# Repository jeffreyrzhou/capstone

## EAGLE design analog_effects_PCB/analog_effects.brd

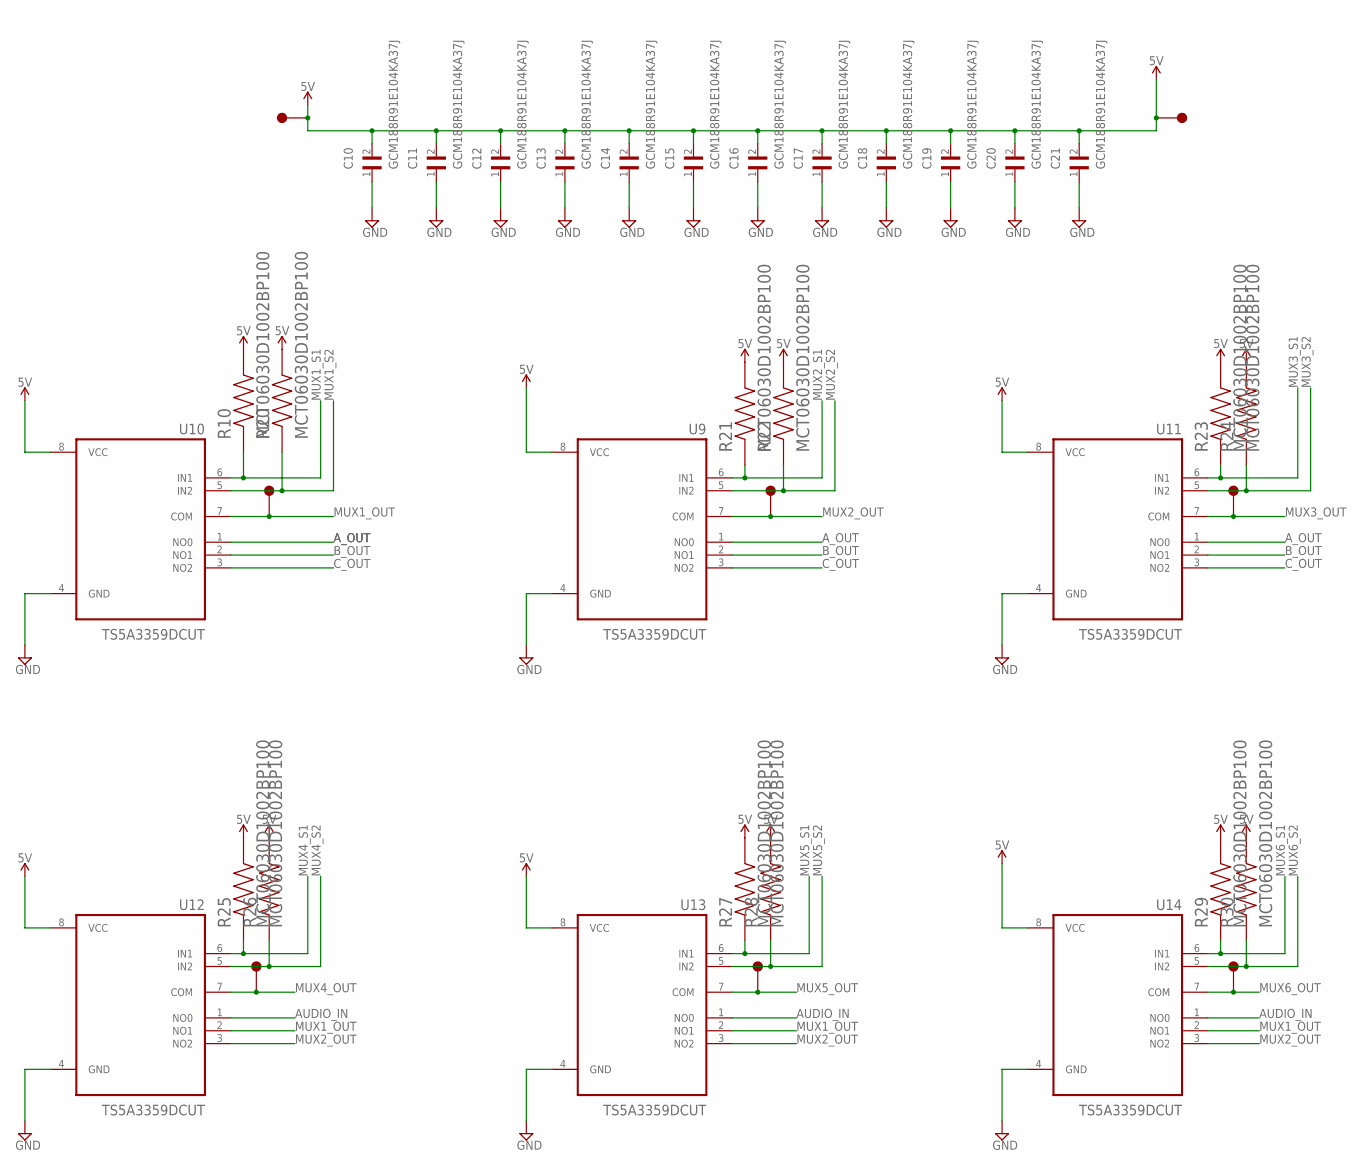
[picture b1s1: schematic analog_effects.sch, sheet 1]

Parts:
C10, C11, C12, C13, C14, C15, C16, C17, C18, C19, C20, C21: GCM188R91E104KA37J; CAPC1608X90N
R10, R20, R21, R22, R23, R24, R25, R26, R27, R28, R29, R30: MCT06030D1002BP100; RESC1508X55N
TP13, TP14, TP15, TP16, TP17, TP18, TP19, TP20: 5015; KEYSTONE_5015
U9, U10, U11, U12, U13, U14: TS5A3359DCUT; SOP50P310X90-8N

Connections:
5V: C10.2, C11.2, C12.2, C13.2, C14.2, C15.2, C16.2, C17.2, C18.2, C19.2, C20.2, C21.2, R10.2, R20.2, R21.2, R22.2, R23.2, R24.2, R25.2, R26.2, R27.2, R28.2, R29.2, R30.2, TP19.1, TP20.1, U9.8 (VCC), U10.8 (VCC), U11.8 (VCC), U12.8 (VCC), U13.8 (VCC), U14.8 (VCC); also elsewhere on the board
AUDIO_IN: U12.1 (NO0), U13.1 (NO0), U14.1 (NO0); also elsewhere on the board
A_OUT: U9.1 (NO0), U10.1 (NO0), U11.1 (NO0); also elsewhere on the board
B_OUT: U9.2 (NO1), U10.2 (NO1), U11.2 (NO1); also elsewhere on the board
C_OUT: U9.3 (NO2), U10.3 (NO2), U11.3 (NO2)
GND: C10.1, C11.1, C12.1, C13.1, C14.1, C15.1, C16.1, C17.1, C18.1, C19.1, C20.1, C21.1, U9.4 (GND), U10.4 (GND), U11.4 (GND), U12.4 (GND), U13.4 (GND), U14.4 (GND); also elsewhere on the board
MUX1_OUT: TP16.1, U10.7 (COM), U12.2 (NO1), U13.2 (NO1), U14.2 (NO1)
MUX1_S1: R10.1, U10.6 (IN1); also elsewhere on the board
MUX1_S2: R20.1, U10.5 (IN2); also elsewhere on the board
MUX2_OUT: TP17.1, U9.7 (COM), U12.3 (NO2), U13.3 (NO2), U14.3 (NO2)
MUX2_S1: R21.1, U9.6 (IN1); also elsewhere on the board
MUX2_S2: R22.1, U9.5 (IN2); also elsewhere on the board
MUX3_OUT: TP18.1, U11.7 (COM)
MUX3_S1: R23.1, U11.6 (IN1); also elsewhere on the board
MUX3_S2: R24.1, U11.5 (IN2); also elsewhere on the board
MUX4_OUT: TP13.1, U12.7 (COM); also elsewhere on the board
MUX4_S1: R25.1, U12.6 (IN1); also elsewhere on the board
MUX4_S2: R26.1, U12.5 (IN2); also elsewhere on the board
MUX5_OUT: TP14.1, U13.7 (COM); also elsewhere on the board
MUX5_S1: R27.1, U13.6 (IN1); also elsewhere on the board
MUX5_S2: R28.1, U13.5 (IN2); also elsewhere on the board
MUX6_OUT: TP15.1, U14.7 (COM); also elsewhere on the board
MUX6_S1: R29.1, U14.6 (IN1); also elsewhere on the board
MUX6_S2: R30.1, U14.5 (IN2); also elsewhere on the board

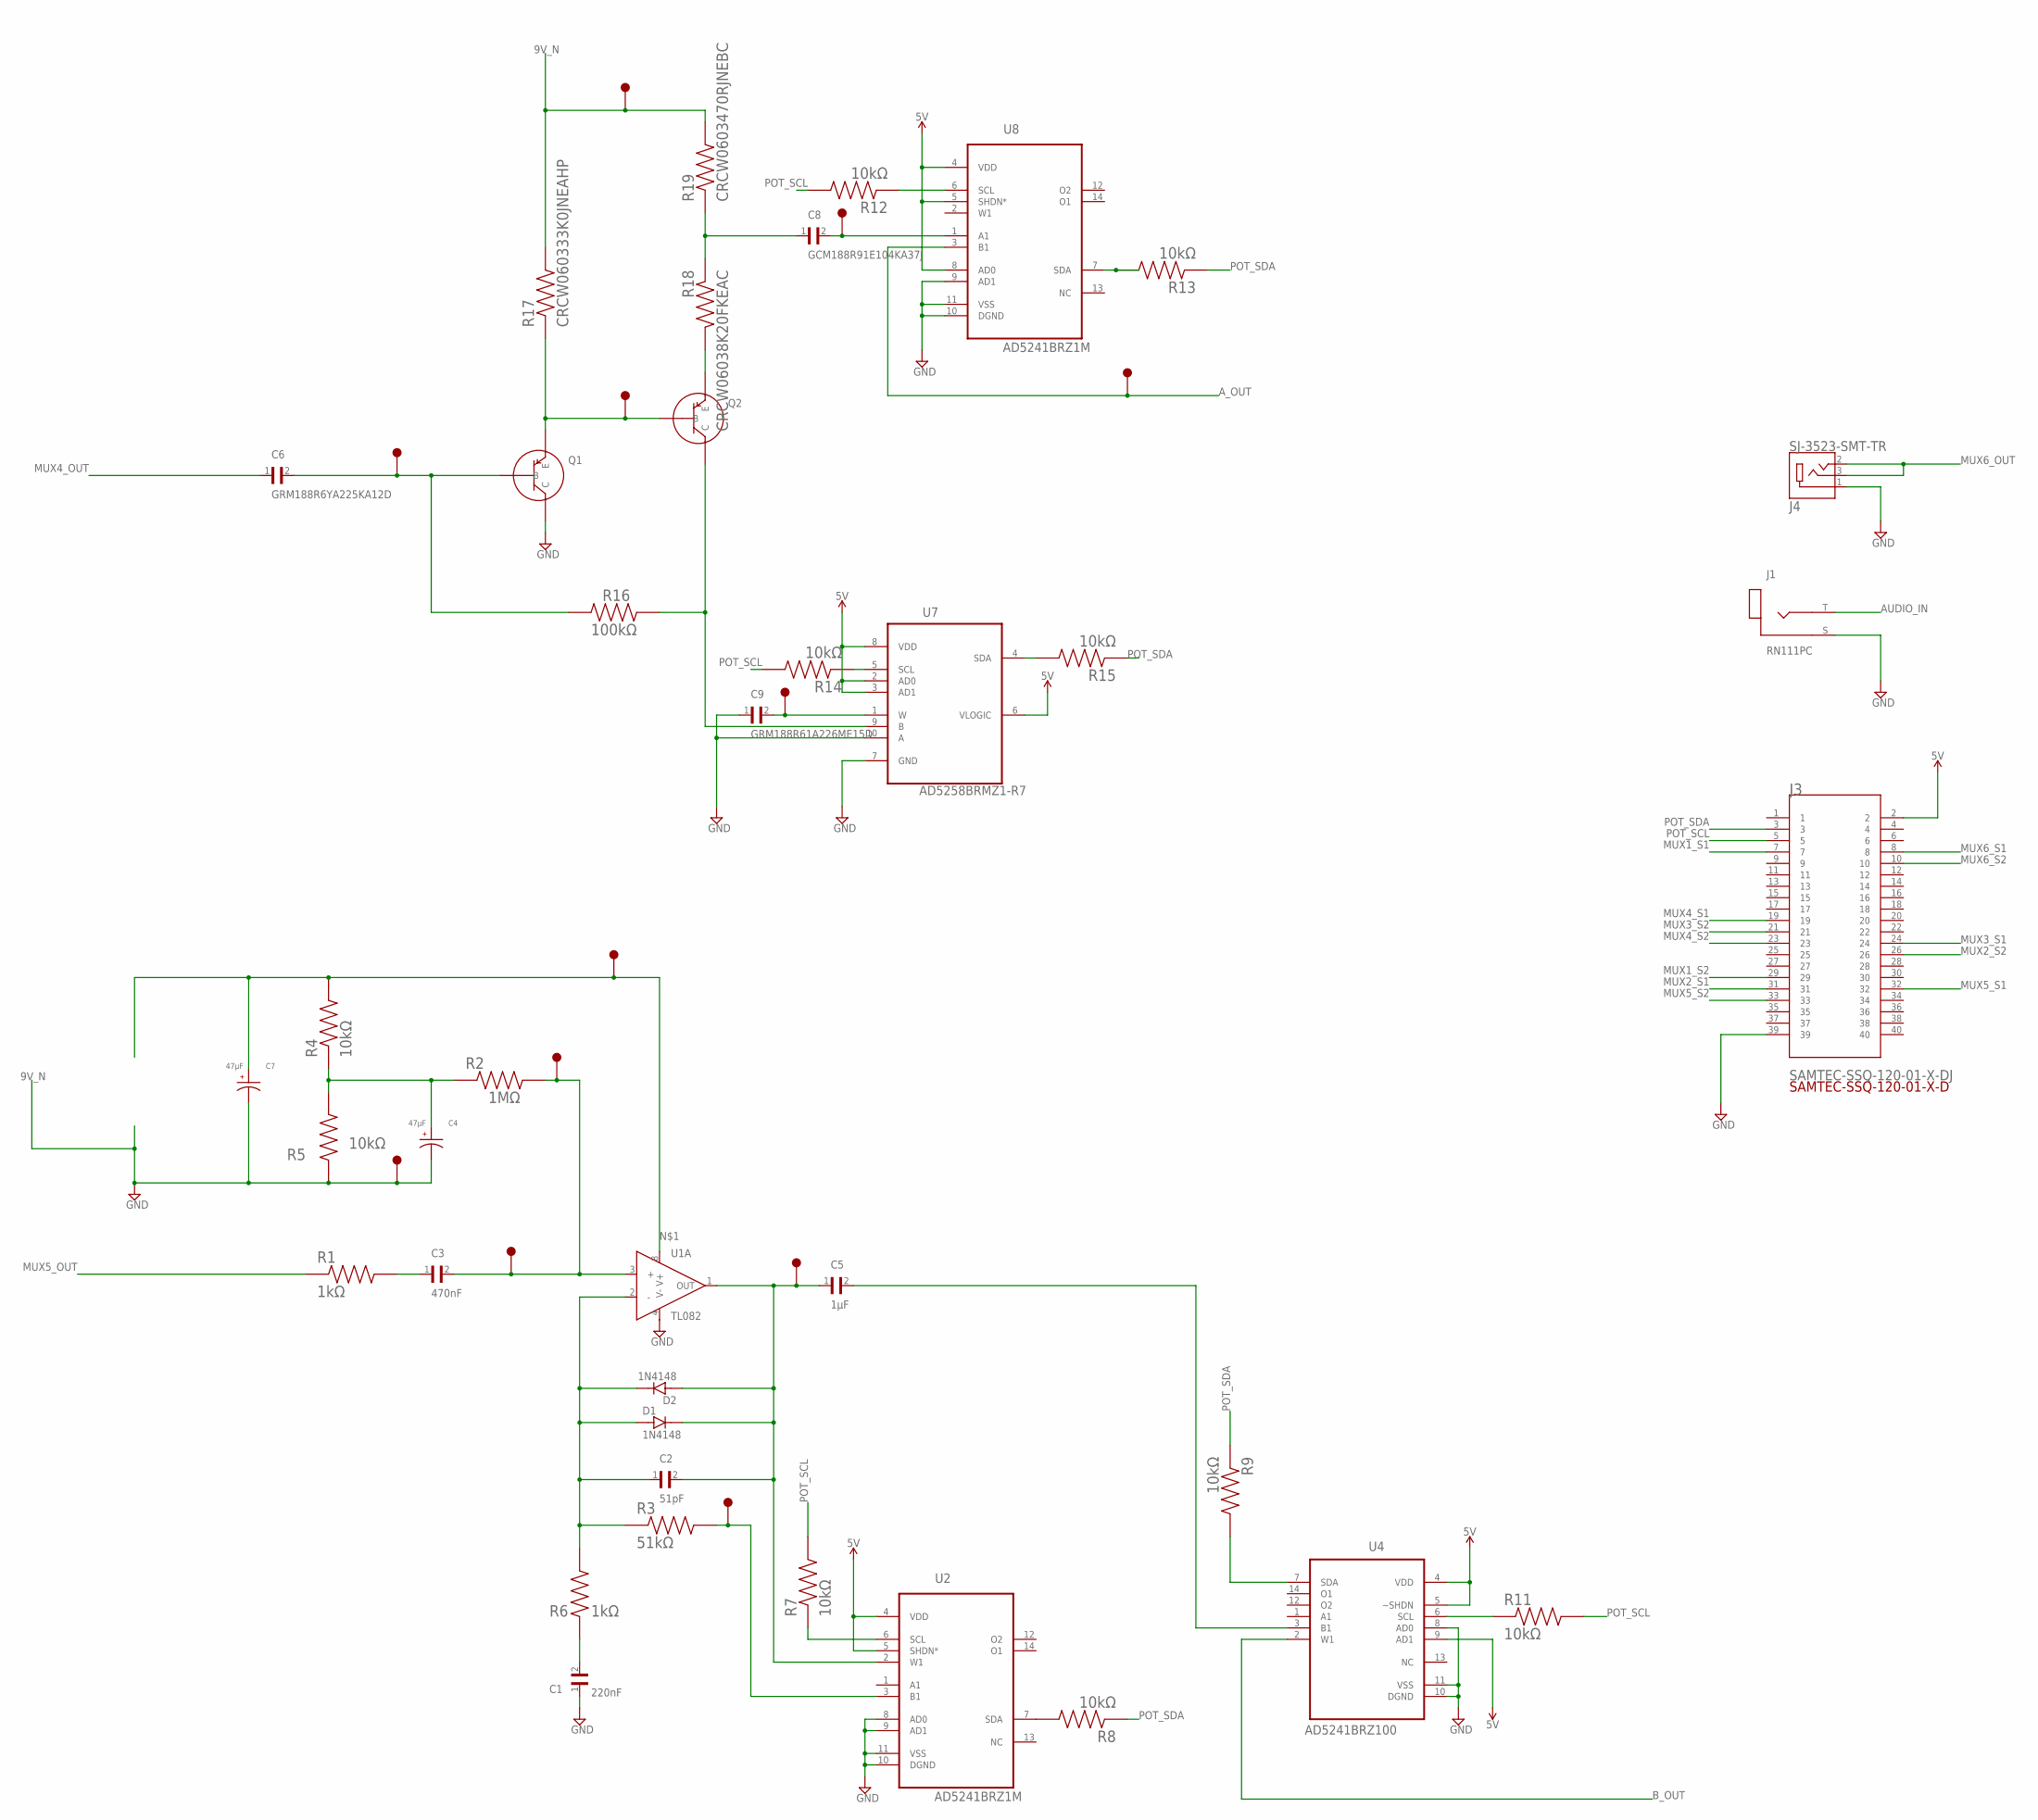
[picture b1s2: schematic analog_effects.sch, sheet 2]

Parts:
C1: 220nF; CAPC3325X94N
C2: 51pF; CAPC1608X87N
C3: 470nF; CAPC1608X95N
C4, C7: 47μF; CAPAE660X800N
C5: 1μF; CAPC1608X90N
C6: GRM188R6YA225KA12D; CAPC1608X90N
C8: GCM188R91E104KA37J; CAPC1608X90N
C9: GRM188R61A226ME15D; CAPC1608X100N
D1, D2: 1N4148; DIOAD829W49L456D191
J1: RN111PC; SWITCHCRAFT_RN111PC
J3: SAMTEC-SSQ-120-01-X-DJ; SAMTEC-SSQ-120-01-X-D
J4: SJ-3523-SMT-TR; CUI_SJ-3523-SMT-TR
R1, R6: 1kΩ; RESC1508X55N
R2: 1MΩ; RESC1608X55N
R3: 51kΩ; RESC1608X55N
R4, R5, R7, R8, R9, R11, R12, R13, R14, R15: 10kΩ; RESC1508X55N
R16: 100kΩ; RESC1508X50N
R17: CRCW060333K0JNEAHP; RESC1608X55N
R18: CRCW06038K20FKEAC; RESC1608X55N
R19: CRCW0603470RJNEBC; RESC1608X55N
TP1, TP2, TP3, TP4, TP5, TP6, TP7, TP8, TP9, TP10, TP11, TP12: 5015; KEYSTONE_5015
U1: TL082; SOIC127P600X175-8N
U2, U8: AD5241BRZ1M; SOIC127P600X175-14N
U4: AD5241BRZ100; SOIC127P600X175-14N
U7: AD5258BRMZ1-R7; SOP50P490X110-10N

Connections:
5V: J3.2, U2.4 (VDD), U2.5 (SHDN*), U4.4 (VDD), U4.5 (~SHDN), U4.9 (AD1), U7.2 (AD0), U7.3 (AD1), U7.6 (VLOGIC), U7.8 (VDD), U8.4 (VDD), U8.5 (SHDN*), U8.8 (AD0); also elsewhere on the board
9V_N: C4.2, C7.2, R5.1, R17.2, R19.2, TP2.1, TP9.1
AUDIO_IN: J1.T; also elsewhere on the board
A_OUT: TP12.1, U8.3 (B1); also elsewhere on the board
B_OUT: U4.2 (W1); also elsewhere on the board
GND: C1.1, C9.1, J1.S, J3.39, J4.1, U1.4 (V-), U2.8 (AD0), U2.9 (AD1), U2.10 (DGND), U2.11 (VSS), U4.8 (AD0), U4.10 (DGND), U4.11 (VSS), U7.7 (GND), U7.10 (A), U8.9 (AD1), U8.10 (DGND), U8.11 (VSS); also elsewhere on the board
MUX1_S1: J3.7; also elsewhere on the board
MUX1_S2: J3.29; also elsewhere on the board
MUX2_S1: J3.31; also elsewhere on the board
MUX2_S2: J3.26; also elsewhere on the board
MUX3_S1: J3.24; also elsewhere on the board
MUX3_S2: J3.21; also elsewhere on the board
MUX4_OUT: C6.1; also elsewhere on the board
MUX4_S1: J3.19; also elsewhere on the board
MUX4_S2: J3.23; also elsewhere on the board
MUX5_OUT: R1.1; also elsewhere on the board
MUX5_S1: J3.32; also elsewhere on the board
MUX5_S2: J3.33; also elsewhere on the board
MUX6_OUT: J4.2, J4.3; also elsewhere on the board
MUX6_S1: J3.8; also elsewhere on the board
MUX6_S2: J3.10; also elsewhere on the board
unnamed: C7.1, R4.2, TP5.1, U1.8 (V+)
unnamed: C4.1, R2.1, R4.1, R5.2
unnamed: C2.1, D1.A, D2.C, R3.1, R6.2, U1.2 (-)
unnamed: C3.1, R1.2
unnamed: C2.2, C5.1, D1.C, D2.A, TP1.1, U1.1 (OUT), U2.2 (W1)
unnamed: C3.2, R2.2, TP3.1, TP4.1, U1.3 (+)
unnamed: C1.2, R6.1
unnamed: C6.2, R16.1, TP7.1
unnamed: R17.1, TP8.1
unnamed: R8.2, U2.7 (SDA)
unnamed: R3.2, TP6.1, U2.3 (B1)
unnamed: R12.1, U8.6 (SCL)
unnamed: R9.2, U4.7 (SDA)
unnamed: R7.1, U2.6 (SCL)
unnamed: C8.1, R18.1, R19.1
unnamed: R13.2, U8.7 (SDA)
unnamed: R14.1, U7.5 (SCL)
unnamed: R11.1, U4.6 (SCL)
unnamed: C5.2, U4.3 (B1)
unnamed: R15.2, U7.4 (SDA)
unnamed: R16.2, U7.9 (B)
unnamed: C9.2, TP11.1, U7.1 (W)
unnamed: C8.2, TP10.1, U8.1 (A1)
POT_SCL: J3.5, R7.2, R11.2, R12.2, R14.2
POT_SDA: J3.3, R8.1, R9.1, R13.1, R15.1

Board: 4 copper layers, 87 parts (0 on the bottom side), 50 nets, no tracks yet.

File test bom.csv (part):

"Part";"Value";"Device";"Package";"Description";"AVAILABILITY";"COMMENT";"CUI_PURCHASE_URL";"DESCRIPTION";"DIGI-KEY_PART_NUMBER";"EU_ROHS_COMPLIANCE";"MF";"MP";"PACKAGE";"POWER_RATING";"PRICE";"PURCHASE-URL";"RESISTANCE";"SPICEPREFIX";"TOLERANCE";"VOLTAGE_RATING";
"C1";"220nF";"12105C224MAT2A";"CAPC3325X94N";"Cap Ceramic 0.22uF 50V X7R 20% SMD 1210 125°C Paper T/R Check prices";"Good";"";"";" 1210 220 nF 50 V ±20 % Tolerance X7R SMT Multilayer Ceramic Capacitor ";"";"";"AVX";"12105C224MAT2A";"3325 AVX";"";"None";"https://pricing.snapeda.com/search/part/12105C224MAT2A/?ref=eda";"";"";"";"";
"C2";"51pF";"C0603C510F1GACTU";"CAPC1608X87N";"Cap Ceramic 51pF 100V C0G 1% SMD 0603 125°C Paper T/R Check prices";"Bad";"";"";" Cap Ceramic 51pF 100V C0G 1% Pad SMD 0603 125°C Extreme Low ESR T/R ";"";"";"KEMET";"C0603C510F1GACTU";"1608 KEMET";"";"None";"";"";"";"";"";
"C3";"470nF";"CGA3E3X7R1H474M080AE";"CAPC1608X95N";"Cap Ceramic 0.47uF 50V X7R 20% Pad SMD 0603 125C Automotive T/R Check prices";"Good";"";"";" CGA Series 0603 470 nF 50 V ±20 % Tolerance X7R SMT Multilayer Ceramic Capacitor ";"";"";"TDK";"CGA3E3X7R1H474M080AE";"1608 TDK";"";"None";"https://pricing.snapeda.com/search/part/CGA3E3X7R1H474M080AE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";"";"";"";"";
"C4";"47μF";"EEE-HC1E470XP";"CAPAE660X800N";"47µF 25V Aluminum Electrolytic Capacitors Radial, Can - SMD 3000 Hrs @ 105°C Check prices";"Good";"";"";" 47µF 25V Aluminum Electrolytic Capacitors Radial, Can - SMD 3000 Hrs @ 105°C ";"";"";"Panasonic Electronic";"EEE-HC1E470XP";"Radial Panasonic";"";"None";"https://pricing.snapeda.com/search/part/EEE-HC1E470XP/?ref=eda";"";"";"";"";
"C5";"1μF";"GCM188R71C105KA64J";"CAPC1608X90N";"Check prices";"Good";"";"";" SMD Capacitor X7R(EIA) with Capacitance: 1.0uF Tol. 10%. Rated Voltage: 16Vdc ";"";"";"Murata";"GCM188R71C105KA64J";"1608 Murata";"";"None";"https://pricing.snapeda.com/search/part/GCM188R71C105KA64J/?ref=eda";"";"";"";"";
"C6";"GRM188R6YA225KA12D";"GRM188R6YA225KA12D";"CAPC1608X90N";"SMD Capacitor X5R(EIA) with Capacitance: 2.2uF Tol. 10%. Rated Voltage: 35Vdc Check prices";"Warning";"";"";" SMD capacitor X5R(EIA) with capacitance 2.2uF Tol.10%. Rated voltage 35Vdc 85C ";"";"";"Murata";"GRM188R6YA225KA12D";"1608 Murata";"";"None";"https://pricing.snapeda.com/search/part/GRM188R6YA225KA12D/?ref=eda";"";"";"";"";
"C7";"47μF";"EEE-HC1E470XP";"CAPAE660X800N";"47µF 25V Aluminum Electrolytic Capacitors Radial, Can - SMD 3000 Hrs @ 105°C Check prices";"Good";"";"";" 47µF 25V Aluminum Electrolytic Capacitors Radial, Can - SMD 3000 Hrs @ 105°C ";"";"";"Panasonic Electronic";"EEE-HC1E470XP";"Radial Panasonic";"";"None";"https://pricing.snapeda.com/search/part/EEE-HC1E470XP/?ref=eda";"";"";"";"";
"C8";"GRM1857U1A103JA44D";"GRM1857U1A103JA44D";"CAPC1608X50N";"Check prices";"Good";"";"";" SMD Capacitor U2J(EIA) with Capacitance: 10000pF Tol. 5%. Rated Voltage: 10Vdc ";"";"";"Murata";"GRM1857U1A103JA44D";"1608 Murata";"";"None";"https://pricing.snapeda.com/search/part/GRM1857U1A103JA44D/?ref=eda";"";"";"";"";
"C9";"GRM188R61A226ME15D";"GRM188R61A226ME15D";"CAPC1608X100N";"SMD Capacitor X5R(EIA) with Capacitance: 22uF Tol. 20%. Rated Voltage: 10Vdc Check prices";"Good";"";"";" SMD capacitor X5R(EIA) with capacitance 22uF Tol.20%. Rated voltage 10Vdc 85C ";"";"";"Murata Electronics";"GRM188R61A226ME15D";"1608 Murata";"";"None";"https://pricing.snapeda.com/search/part/GRM188R61A226ME15D/?ref=eda";"";"C";"";"";
"C10";"GCM188R91E104KA37J";"GCM188R91E104KA37J";"CAPC1608X90N";"SMD Capacitor X8R(EIA) with Capacitance: 0.10uF Tol. 10%. Rated Voltage: 25Vdc Check prices";"Warning";"";"";" SMD capacitor X8R(EIA) with capacitance 0.10uF Tol.10%. Rated voltage 25Vdc 150C ";"";"";"Murata";"GCM188R91E104KA37J";"1608 Murata";"";"None";"https://pricing.snapeda.com/search/part/GCM188R91E104KA37J/?ref=eda";"";"";"";"";
"C11";"GCM188R91E104KA37J";"GCM188R91E104KA37J";"CAPC1608X90N";"SMD Capacitor X8R(EIA) with Capacitance: 0.10uF Tol. 10%. Rated Voltage: 25Vdc Check prices";"Warning";"";"";" SMD capacitor X8R(EIA) with capacitance 0.10uF Tol.10%. Rated voltage 25Vdc 150C ";"";"";"Murata";"GCM188R91E104KA37J";"1608 Murata";"";"None";"https://pricing.snapeda.com/search/part/GCM188R91E104KA37J/?ref=eda";"";"";"";"";
"C12";"GCM188R91E104KA37J";"GCM188R91E104KA37J";"CAPC1608X90N";"SMD Capacitor X8R(EIA) with Capacitance: 0.10uF Tol. 10%. Rated Voltage: 25Vdc Check prices";"Warning";"";"";" SMD capacitor X8R(EIA) with capacitance 0.10uF Tol.10%. Rated voltage 25Vdc 150C ";"";"";"Murata";"GCM188R91E104KA37J";"1608 Murata";"";"None";"https://pricing.snapeda.com/search/part/GCM188R91E104KA37J/?ref=eda";"";"";"";"";
"C13";"GCM188R91E104KA37J";"GCM188R91E104KA37J";"CAPC1608X90N";"SMD Capacitor X8R(EIA) with Capacitance: 0.10uF Tol. 10%. Rated Voltage: 25Vdc Check prices";"Warning";"";"";" SMD capacitor X8R(EIA) with capacitance 0.10uF Tol.10%. Rated voltage 25Vdc 150C ";"";"";"Murata";"GCM188R91E104KA37J";"1608 Murata";"";"None";"https://pricing.snapeda.com/search/part/GCM188R91E104KA37J/?ref=eda";"";"";"";"";
"C14";"GCM188R91E104KA37J";"GCM188R91E104KA37J";"CAPC1608X90N";"SMD Capacitor X8R(EIA) with Capacitance: 0.10uF Tol. 10%. Rated Voltage: 25Vdc Check prices";"Warning";"";"";" SMD capacitor X8R(EIA) with capacitance 0.10uF Tol.10%. Rated voltage 25Vdc 150C ";"";"";"Murata";"GCM188R91E104KA37J";"1608 Murata";"";"None";"https://pricing.snapeda.com/search/part/GCM188R91E104KA37J/?ref=eda";"";"";"";"";
"C15";"GCM188R91E104KA37J";"GCM188R91E104KA37J";"CAPC1608X90N";"SMD Capacitor X8R(EIA) with Capacitance: 0.10uF Tol. 10%. Rated Voltage: 25Vdc Check prices";"Warning";"";"";" SMD capacitor X8R(EIA) with capacitance 0.10uF Tol.10%. Rated voltage 25Vdc 150C ";"";"";"Murata";"GCM188R91E104KA37J";"1608 Murata";"";"None";"https://pricing.snapeda.com/search/part/GCM188R91E104KA37J/?ref=eda";"";"";"";"";
"C16";"GCM188R91E104KA37J";"GCM188R91E104KA37J";"CAPC1608X90N";"SMD Capacitor X8R(EIA) with Capacitance: 0.10uF Tol. 10%. Rated Voltage: 25Vdc Check prices";"Warning";"";"";" SMD capacitor X8R(EIA) with capacitance 0.10uF Tol.10%. Rated voltage 25Vdc 150C ";"";"";"Murata";"GCM188R91E104KA37J";"1608 Murata";"";"None";"https://pricing.snapeda.com/search/part/GCM188R91E104KA37J/?ref=eda";"";"";"";"";
"C17";"GCM188R91E104KA37J";"GCM188R91E104KA37J";"CAPC1608X90N";"SMD Capacitor X8R(EIA) with Capacitance: 0.10uF Tol. 10%. Rated Voltage: 25Vdc Check prices";"Warning";"";"";" SMD capacitor X8R(EIA) with capacitance 0.10uF Tol.10%. Rated voltage 25Vdc 150C ";"";"";"Murata";"GCM188R91E104KA37J";"1608 Murata";"";"None";"https://pricing.snapeda.com/search/part/GCM188R91E104KA37J/?ref=eda";"";"";"";"";
"C18";"GCM188R91E104KA37J";"GCM188R91E104KA37J";"CAPC1608X90N";"SMD Capacitor X8R(EIA) with Capacitance: 0.10uF Tol. 10%. Rated Voltage: 25Vdc Check prices";"Warning";"";"";" SMD capacitor X8R(EIA) with capacitance 0.10uF Tol.10%. Rated voltage 25Vdc 150C ";"";"";"Murata";"GCM188R91E104KA37J";"1608 Murata";"";"None";"https://pricing.snapeda.com/search/part/GCM188R91E104KA37J/?ref=eda";"";"";"";"";
"C19";"GCM188R91E104KA37J";"GCM188R91E104KA37J";"CAPC1608X90N";"SMD Capacitor X8R(EIA) with Capacitance: 0.10uF Tol. 10%. Rated Voltage: 25Vdc Check prices";"Warning";"";"";" SMD capacitor X8R(EIA) with capacitance 0.10uF Tol.10%. Rated voltage 25Vdc 150C ";"";"";"Murata";"GCM188R91E104KA37J";"1608 Murata";"";"None";"https://pricing.snapeda.com/search/part/GCM188R91E104KA37J/?ref=eda";"";"";"";"";
"C20";"GCM188R91E104KA37J";"GCM188R91E104KA37J";"CAPC1608X90N";"SMD Capacitor X8R(EIA) with Capacitance: 0.10uF Tol. 10%. Rated Voltage: 25Vdc Check prices";"Warning";"";"";" SMD capacitor X8R(EIA) with capacitance 0.10uF Tol.10%. Rated voltage 25Vdc 150C ";"";"";"Murata";"GCM188R91E104KA37J";"1608 Murata";"";"None";"https://pricing.snapeda.com/search/part/GCM188R91E104KA37J/?ref=eda";"";"";"";"";
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
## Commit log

2021-01-25 added initial spice simulations for overdrive pedal
2021-02-24 added the preamp
2021-02-25 added reimbursement form
2021-02-25 added inital PCB design of preamp
2021-02-26 Adding the Fuzz Circuit Simulation using LTSpice
2021-03-01 added analog effects
2021-03-01 added the schematic for the overdrive analog effect
2021-03-03 added mux and digital pots to schematic
2021-03-04 completed the digital pot circuitry on schematic
2021-03-10 Partly added Fuzz Circuit
2021-03-12 Added Mux logic to schematic. need to connect to Effects and decide if we have effect c or use as pass through
2021-03-12 Fixed Fuzz pot but need to change volume pot to 500k
2021-03-18 Schematic almost finalized missing aux in and out and possibly push buttons, starting layout
2021-03-19 Finalized schematic with connectos, next step layout
2021-04-15 Adding all files that were needed, Capstone is completed and it worked
2021-04-15 Adding some more files

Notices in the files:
parts and their libraries:
SparkFun-PowerSymbols: Licensing: Creative Commons ShareAlike 4.0 International - https://creativecommons.org/licenses/by-sa/4.0
